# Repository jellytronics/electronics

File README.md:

electronics
===========

My electronics stuff

This project(s) will be suspended indefinitely from 11th March 2014.

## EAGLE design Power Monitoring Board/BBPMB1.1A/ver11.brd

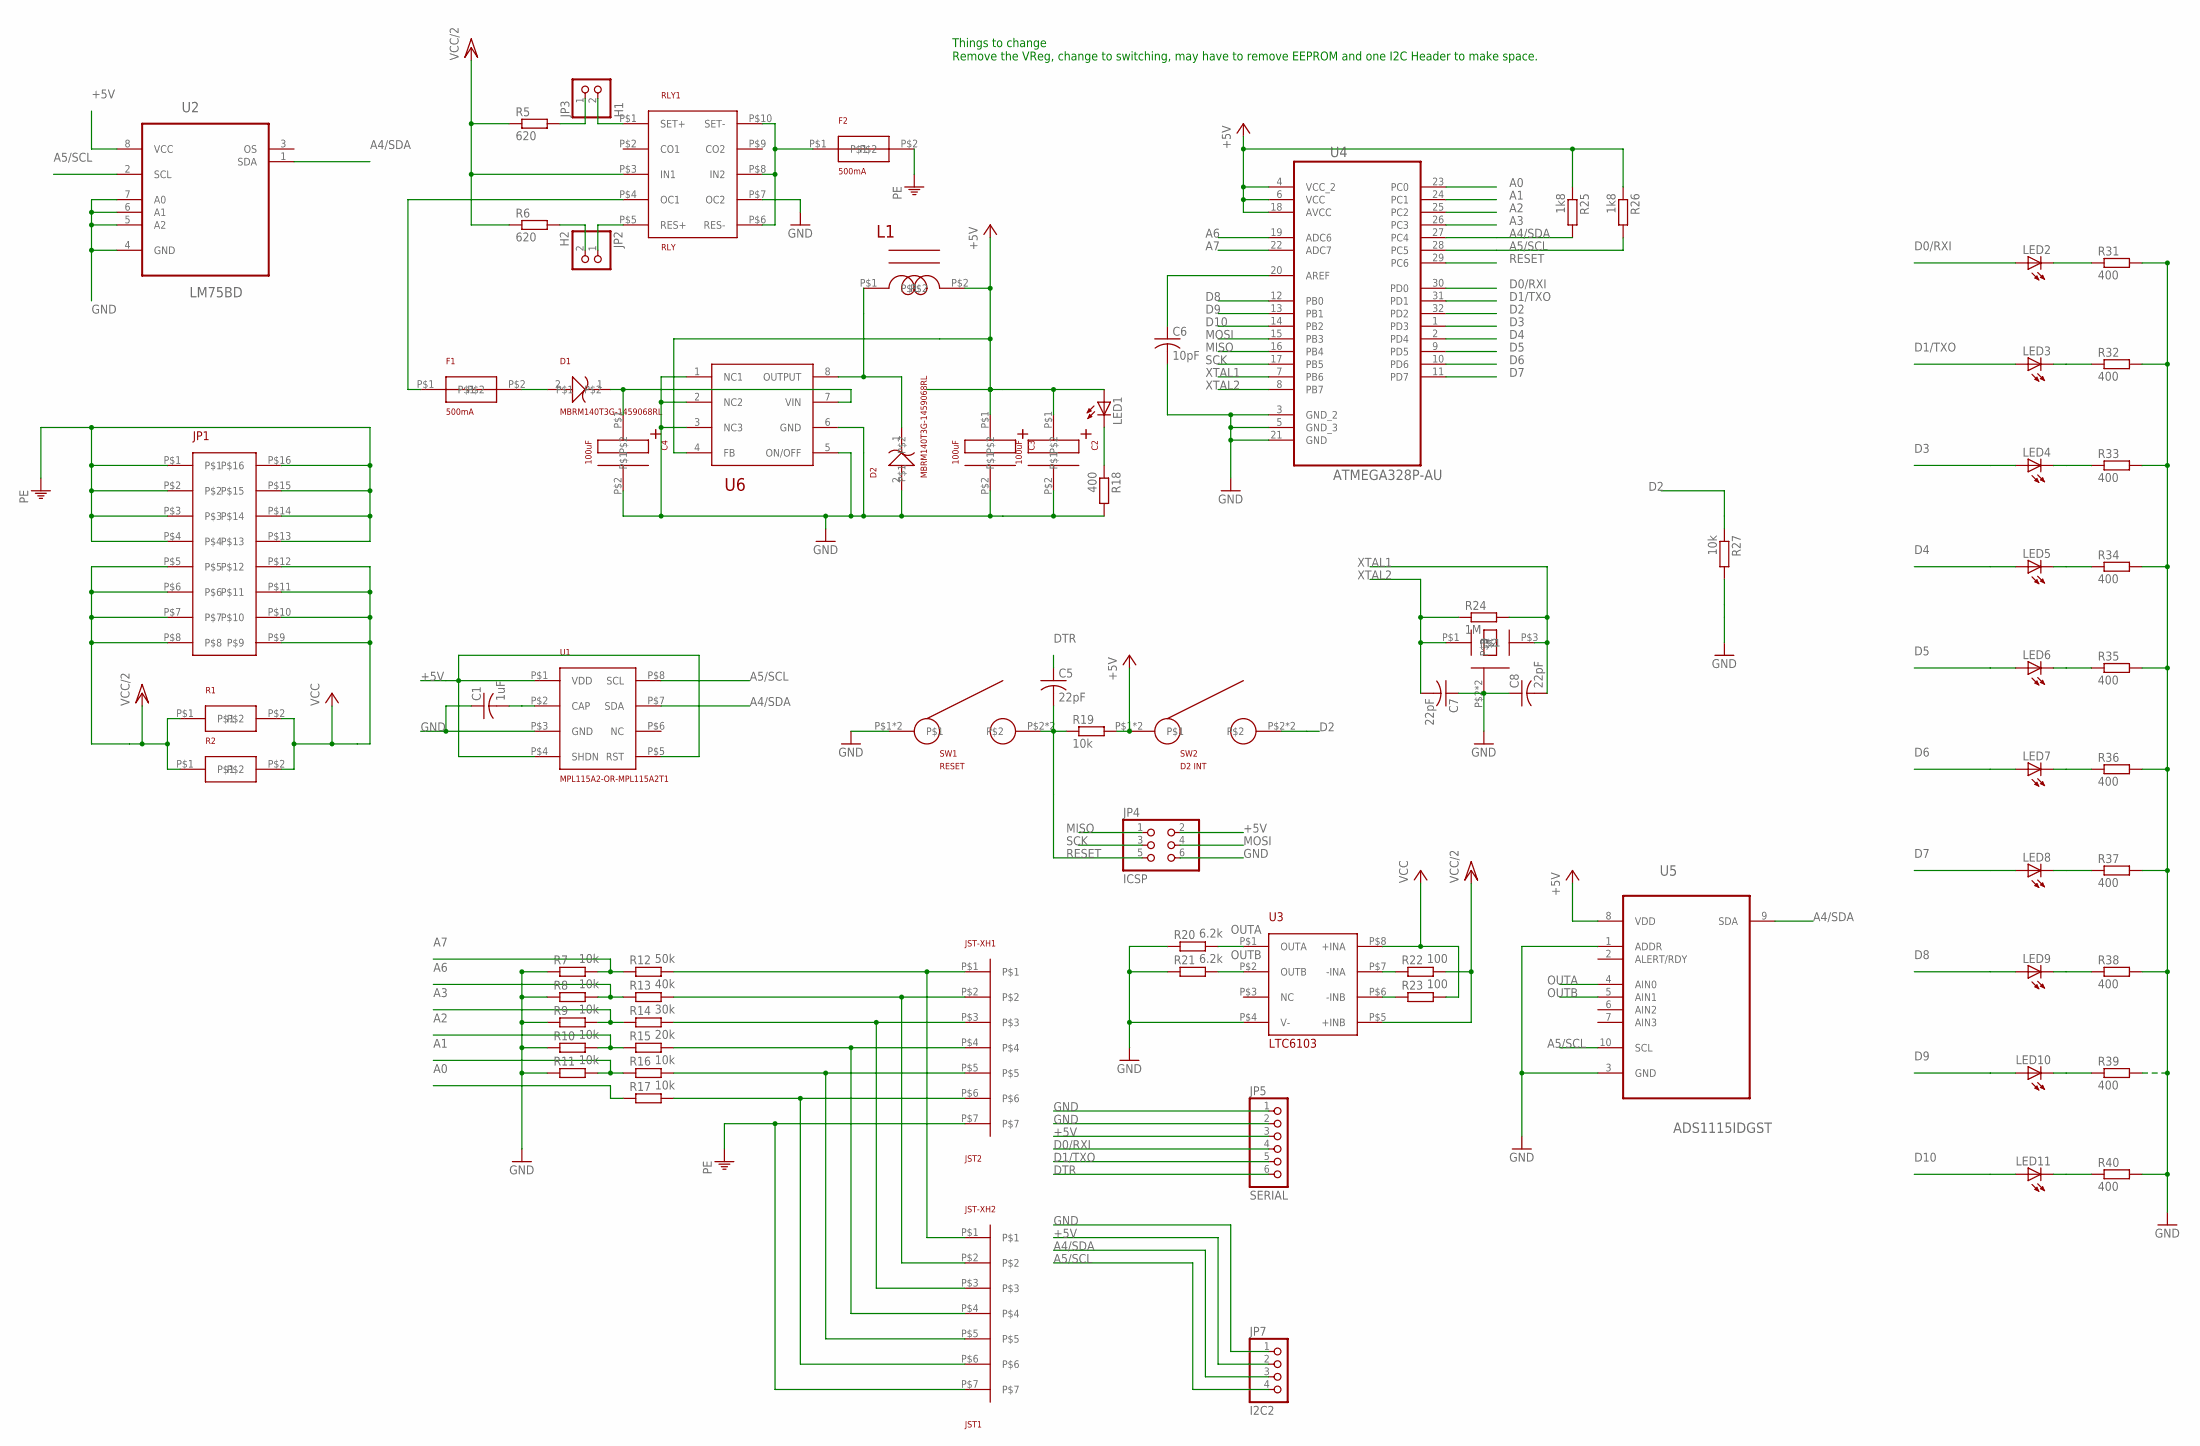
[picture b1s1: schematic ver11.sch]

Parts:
C1: 1uF; C1206
C2, C3, C4: 100uF; EEEFTH101XAP
C5, C7, C8: 22pF; C1206
C6: 10pF; C1206
D1, D2: MBRM140T3G-1459068RL
F1: 500mA; MF-MSMF050-2
F2: 500mA; 0154.500DR-FUSE-0453.500
JP1: 39-29-1167-MOLEX
JP2: H2; 1X02
JP3: H1; 1X02
JP4: ICSP; 2X03
JP5: SERIAL; 1X06
JP7: I2C2; 1X04
JST-XH1: JST2; JSTXH-7PIN
JST-XH2: JST1; JSTXH-7PIN
L1: MCSD75-121KU-120UF-INDUCTOR-660MA-1864147
LED1, LED2, LED3, LED4, LED5, LED6, LED7, LED8, LED9, LED10, LED11: LED1206; LED-1206
R1, R2: OARSXPR002FLF
R5, R6: 620; R1206
R7, R8, R9, R10, R11, R16, R17, R19, R27: 10k; R1206
R12: 50k; R1206
R13: 40k; R1206
R14: 30k; R1206
R15: 20k; R1206
R18, R31, R32, R33, R34, R35, R36, R37, R38, R39, R40: 400; R1206
R20, R21: 6.2k; R1206
R22, R23: 100; R1206
R24: 1M; R1206
R25, R26: 1k8; R1206
RLY1: RLY; 3-1393788-3
SW1: RESET; MC32829
SW2: D2 INT; MC32829
U1: MPL115A2-OR-MPL115A2T1
U2: LM75BD; SOIC127P600X175-8N
U3: LTC6103; LTC6103CMS8#PBF
U4: ATMEGA328P-AU; QFP80P900X900X120-32N
U5: ADS1115IDGST; SOP50P490X110-10N
U6: VOLTREG-LM2594MX-5.0/NOPB-1496090; SO08
XT1: ABMM2-16.000MHZ-E2-T

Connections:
+5V: C2.P$1, C3.P$1, JP4.2, JP5.3, JP7.2, L1.P$2, LED1.A, R19.2, R25.1, R26.1, SW2.P$1, SW2.P$4, U1.P$1 (VDD), U1.P$4 (SHDN), U1.P$5 (RST), U2.8 (VCC), U4.4 (VCC_2), U4.6 (VCC), U4.18 (AVCC), U5.8 (VDD), U6.4 (FB)
A0: R17.1, U4.23 (PC0)
A1: R11.2, R16.1, U4.24 (PC1)
A2: R10.2, R15.1, U4.25 (PC2)
A3: R9.2, R14.1, U4.26 (PC3)
A4/SDA: JP7.3, R25.2, U1.P$7 (SDA), U2.1 (SDA), U4.27 (PC4), U5.9 (SDA)
A5/SCL: JP7.4, R26.2, U1.P$8 (SCL), U2.2 (SCL), U4.28 (PC5), U5.10 (SCL)
A6: R8.2, R13.1, U4.19 (ADC6)
A7: R7.2, R12.1, U4.22 (ADC7)
D0/RXI: JP5.4, LED2.A, U4.30 (PD0)
D1/TXO: JP5.5, LED3.A, U4.31 (PD1)
D2: R27.1, SW2.P$2, SW2.P$3, U4.32 (PD2)
D3: LED4.A, U4.1 (PD3)
D4: LED5.A, U4.2 (PD4)
D5: LED6.A, U4.9 (PD5)
D6: LED7.A, U4.10 (PD6)
D7: LED8.A, U4.11 (PD7)
D8: LED9.A, U4.12 (PB0)
D9: LED10.A, U4.13 (PB1)
D10: LED11.A, U4.14 (PB2)
DTR: C5.1, JP5.6
GND: C1.1, C2.P$2, C3.P$2, C4.P$2, C6.2, C7.1, C8.1, D2.2, JP4.6, JP5.1, JP5.2, JP7.1, R7.1, R8.1, R9.1, R10.1, R11.1, R18.2, R20.1, R21.1, R27.2, R31.2, R32.2, R33.2, R34.2, R35.2, R36.2, R37.2, R38.2, R39.2, R40.2, RLY1.P$7 (OC2), SW1.P$1, SW1.P$4, U1.P$3 (GND), U2.4 (GND), U2.5 (A2), U2.6 (A1), U2.7 (A0), U3.P$4 (V-), U4.3 (GND_2), U4.5 (GND_3), U4.21 (GND), U5.1 (ADDR), U5.3 (GND), U6.1 (NC1), U6.2 (NC2), U6.3 (NC3), U6.5 (ON/OFF), U6.6 (GND), XT1.P$2, XT1.P$4
MISO: JP4.1, U4.16 (PB4)
MOSI: JP4.4, U4.15 (PB3)
unnamed: F1.P$1, RLY1.P$4 (OC1)
unnamed: C4.P$1, D1.1, U6.7 (VIN)
unnamed: D1.2, F1.P$2
unnamed: LED1.C, R18.1
unnamed: JP3.1, R5.2
unnamed: JP3.2, RLY1.P$1 (SET+)
unnamed: LED2.C, R31.1
unnamed: LED3.C, R32.1
unnamed: LED4.C, R33.1
unnamed: LED5.C, R34.1
unnamed: LED6.C, R35.1
unnamed: LED7.C, R36.1
unnamed: LED8.C, R37.1
unnamed: LED9.C, R38.1
unnamed: LED10.C, R39.1
unnamed: LED11.C, R40.1
unnamed: JST-XH1.P$1, JST-XH2.P$1, R12.2
unnamed: JST-XH1.P$2, JST-XH2.P$2, R13.2
unnamed: JST-XH1.P$3, JST-XH2.P$3, R14.2
unnamed: JST-XH1.P$4, JST-XH2.P$4, R15.2
unnamed: JST-XH1.P$5, JST-XH2.P$5, R16.2
unnamed: JST-XH1.P$6, JST-XH2.P$6, R17.2
unnamed: JP2.2, R6.2
unnamed: C6.1, U4.20 (AREF)
unnamed: F2.P$1, RLY1.P$6 (RES-), RLY1.P$8 (IN2), RLY1.P$10 (SET-)
unnamed: JP2.1, RLY1.P$5 (RES+)
unnamed: D2.1, L1.P$1, U6.8 (OUTPUT)
unnamed: R22.1, U3.P$7 (-INA)
unnamed: R23.1, U3.P$6 (-INB)
unnamed: C1.2, U1.P$2 (CAP)
OUTA: R20.2, U3.P$1 (OUTA), U5.4 (AIN0)
OUTB: R21.2, U3.P$2 (OUTB), U5.5 (AIN1)
PE: F2.P$2, JP1.P$1, JP1.P$2, JP1.P$3, JP1.P$4, JP1.P$13, JP1.P$14, JP1.P$15, JP1.P$16, JST-XH1.P$7, JST-XH2.P$7
RESET: C5.2, JP4.5, R19.1, SW1.P$2, SW1.P$3, U4.29 (PC6)
SCK: JP4.3, U4.17 (PB5)
VCC: JP1.P$9, JP1.P$10, JP1.P$11, JP1.P$12, R1.P$2, R2.P$2, R23.2, U3.P$8 (+INA)
VCC/2: JP1.P$5, JP1.P$6, JP1.P$7, JP1.P$8, R1.P$1, R2.P$1, R5.1, R6.1, R22.2, RLY1.P$3 (IN1), U3.P$5 (+INB)
XTAL1: C8.2, R24.2, U4.7 (PB6), XT1.P$3
XTAL2: C7.2, R24.1, U4.8 (PB7), XT1.P$1

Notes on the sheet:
Things to change Remove the VReg, change to switching, may have to remove EEPROM and one I2C Header to make space.

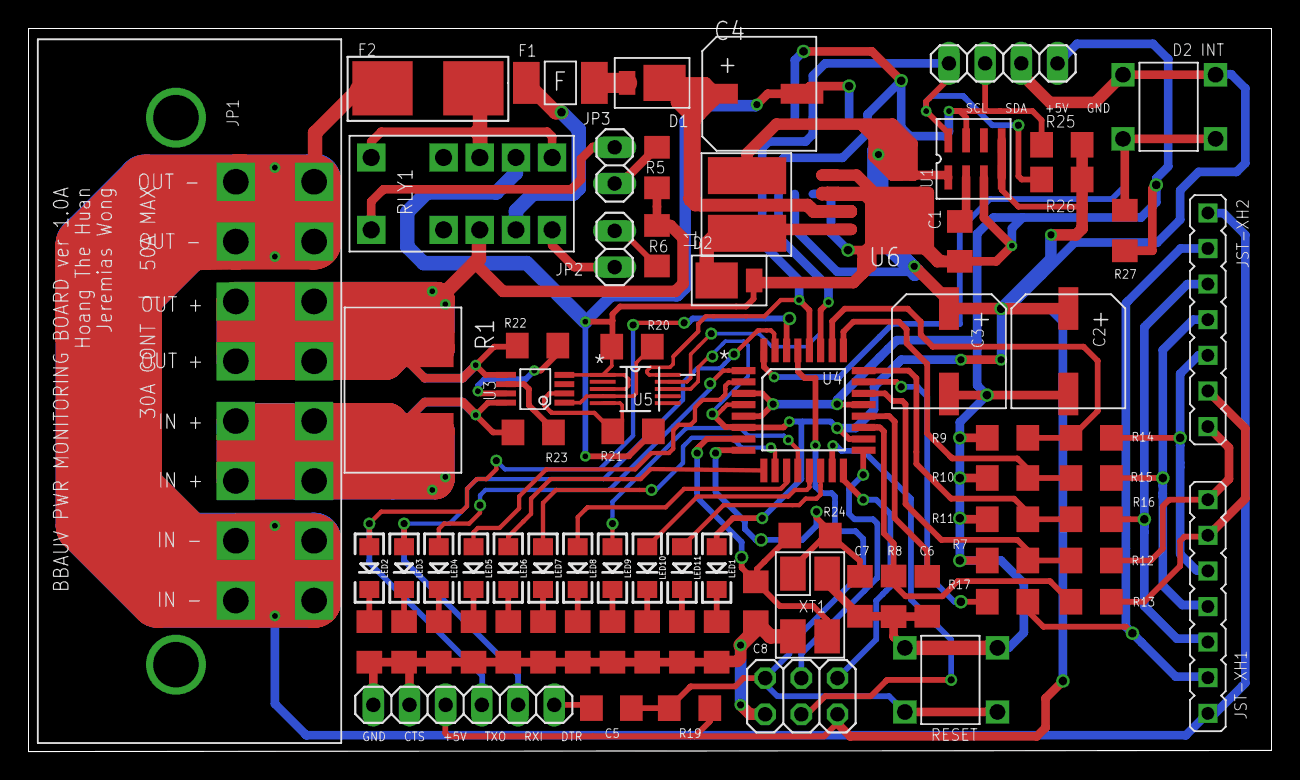
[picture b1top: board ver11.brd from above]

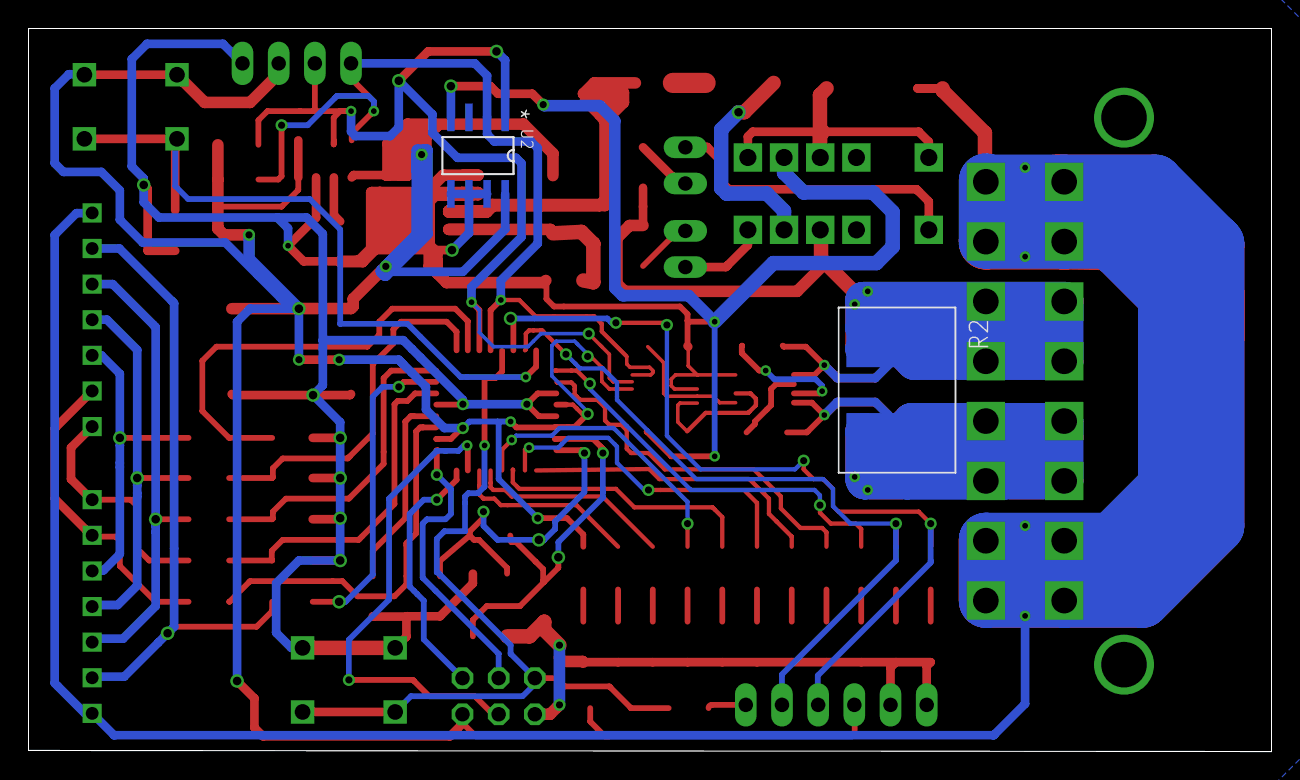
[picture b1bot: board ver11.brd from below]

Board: 2 copper layers, 87.3 x 50.8 mm, 77 parts (2 on the bottom side), 63 nets.

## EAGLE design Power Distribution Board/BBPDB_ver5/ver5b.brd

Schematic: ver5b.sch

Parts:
C1, C2, C3, C4, C18, C21, C22, C23, C24, C40: 0.5uF; C1206
C5, C6, C25, C26, C37, C38, C39: 22pF; C1206
C7, C8, C9, C10, C12, C30, C31, C34, C35: 10uF; C1206
C11, C20, C42, C44, C45, C49, C50, C51, C53, C54: EEEFTH101XAP
C13, C17: 1nF; C1206
C14: 2.2uF; C1206
C15, C16: 0.1uF; C1206
C19: 22uF; C1206
C27, C28, C32, C33: UVY2A221MHD1TO; E5-13
C29, C36, C41, C43, C46, C47, C48, C52: C-USC1206; C1206
C55: 10uF X7R; C1206
C56, C60: 1nF X7R; C1206
C57: 2.2uF X7R; C1206
C58, C59: 0.1uF X7R; C1206
C61: 22uF X7R; C1206
D1, D2, D3, D4, D5, D6, D7, D8, D9, D10: MBRM140T3G-1459068RL
F1, F3: 500mA; MF-MSMF050-2
F2, F4: 0154.500DR-FUSE-0453.500
IC1, IC2: FT4232HL; LQFP64
JP1: 39-29-1167-MOLEX
JP2: POWER IN; 39-29-1167-MOLEX
JP3, JP11: SERIAL_1; 1X03/90
JP4, JP12: SERIAL_2; 1X03/90
JP5, JP13: SERIAL_3; 1X03/90
JP6: HWSERIAL; 1X06
JP7: SBC_SW; 1X02
JP8: I2C; 1X04
JP9: PINHD-2X3; 2X03
JP10: ISCP; 2X03
JP14: SERIAL_4; 1X03/90
JP15, JP16: DC FAN 24V; 1X02
JP17: M4ATX | VBATT | 15A; 39-29-4049-MOLEX
JP18: POWER OUT :: M4 ATX | VIDEORAY | BTD150 | VVREG; 39-29-1167-MOLEX
JP19: 43045-2400
L1, L5: 6.8uH 2292530; LAIRD-TECH-INDUCTOR-TYS5040
L2, L6: 10uH 2292532; LAIRD-TECH-INDUCTOR-TYS5040
L3, L4: SER1360-802KLD-2288814RL-INDUCTOR
LED1, LED2, LED3, LED4, LED5, LED6, LED7, LED8, LED9, LED10, LED11, LED12, LED13, LED14, LED15: LEDCHIPLED_1206; CHIPLED_1206
R1, R24, R54, R55, R56, R57: 300; R1206
R2, R27, R39: 1M; R1206
R3, R4, R5, R6, R28, R29, R30, R31: 24; R1206
R7, R19, R20, R34: 1k; R1206
R8, R35: 12k; R1206
R9, R10, R36, R37: INDUCTOR-AISC-0603-R0082-J-T-1628488; R0603
R11, R21, R38, R50, R51: 100; R1206
R12, R15, R16, R17, R40, R41, R42, R43, R44, R45, R46, R47, R48, R49: 10k; R1206
R13, R66: 31.6k; R1206
R14, R23, R67, R70: 10.2k; R1206
R18, R68: 60.4k; R1206
R22, R69: 53.6k; R1206
R25, R26, R32, R33, R58, R59, R62, R63: 5000; R1206
R52, R53: 1k8; R1206
R60, R61, R64, R65: R-EU_R1206; R1206
SW1: RESET; MC32829
SW2: INT1; MC32829
SW3: INT2; MC32829
U1, U8: ADUM3160BRWZ; SOIC127P1032X265-16N
U2, U10: CAT93C46WI-GT3-1718152-EEPROM; SO08
U3, U18: LT3509EMSEPBF; SOP50P490X110-17N
U4, U5, U6, U12, U13, U14, U15: ISO7221ADR-1575146; SO08
U7: PS2701A-1-F3-A-1682859RL
U9: MPL115A2-OR-MPL115A2T1
U11: ATMEGA328P-AU; QFP80P900X900X120-32N
U16, U17: TPS5450DDARG4; SOIC127P600X170-9N
U$1, U$5: USB-MINIB-5PIN; USB-MINIB
U$2, U$6: ABMM2-12.000MHZ-E2-T; ABMM2-16.000MHZ-E2-T
U$7: ABMM2-16.000MHZ-E2-T
U$8, U$11, U$12, U$13: LTC4416
U$9, U$10, U$14, U$15, U$16, U$17, U$18, U$19, U$20, U$21, U$22, U$23, U$24, U$25, U$26, U$27: IRF9310PBF

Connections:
+1.8_A: C7.2, IC1.12 (VCORE), IC1.37 (VCORE), IC1.50 (VREGIN), IC1.64 (VCORE)
+1.8_B: C30.2, IC2.12 (VCORE), IC2.37 (VCORE), IC2.50 (VREGIN), IC2.64 (VCORE)
+3.3_A: C8.2, C11.P$1, C12.2, IC1.20 (VCCIO), IC1.31 (VCCIO), IC1.42 (VCCIO), IC1.49 (VREGOUT), IC1.56 (VCCIO), L1.1, LED2.A, R7.1, R9.1, R10.1, R12.1, R13.1, R16.1, R17.1, U2.2 (VCC), U2.8 (ORG)
+3.3_B: C31.2, C55.2, IC2.20 (VCCIO), IC2.31 (VCCIO), IC2.42 (VCCIO), IC2.49 (VREGOUT), IC2.56 (VCCIO), L5.1, R34.1, R36.1, R37.1, R46.1, R48.1, R49.1, R66.1, U10.2 (VCC), U10.8 (ORG)
+5V_A: C4.2, C18.2, C19.2, C20.P$1, C40.1, JP6.3, JP8.2, JP9.3, JP9.5, JP10.2, L2.2, LED3.A, R22.1, R38.2, R40.1, R42.1, R44.1, R52.2, R53.2, SW2.P$1, SW2.P$4, SW3.P$1, SW3.P$4, U1.16 (VBUS2), U3.13 (BD), U4.1 (VCC1), U4.8 (VCC2), U5.1 (VCC1), U5.8 (VCC2), U6.1 (VCC1), U6.8 (VCC2), U9.P$1 (VDD), U9.P$4 (SHDN), U9.P$5 (RST), U11.4 (VCC_2), U11.6 (VCC), U11.18 (AVCC)
+5V_B: C24.2, C61.2, L6.2, R69.1, U8.16 (VBUS2), U12.1 (VCC1), U12.8 (VCC2), U13.1 (VCC1), U13.8 (VCC2), U14.1 (VCC1), U14.8 (VCC2), U15.1 (VCC1), U15.8 (VCC2), U18.13 (BD), U$8.P$2 (E1)
A0: LED8.A, U11.23 (PC0)
A1: LED9.A, U11.24 (PC1)
A2: LED10.A, U11.25 (PC2)
A3: LED11.A, U11.26 (PC3)
A4/SDA: JP8.3, R52.1, U9.P$7 (SDA), U11.27 (PC4)
A5/SCL: JP8.4, R53.1, U9.P$8 (SCL), U11.28 (PC5)
A6: U11.19 (ADC6)
A7: U11.22 (ADC7)
D0/RXI: JP6.4, R19.1, U11.30 (PD0)
D1/TXO: JP6.5, R20.1, U11.31 (PD1)
D2: JP9.4, R50.1, SW2.P$2, SW2.P$3, U11.32 (PD2)
D3: JP9.6, R51.1, SW3.P$2, SW3.P$3, U11.1 (PD3)
D4: R41.2, U11.2 (PD4), U$11.P$4 (E2)
D5: R40.2, U11.9 (PD5), U$11.P$2 (E1)
D6: R45.2, U11.10 (PD6), U$13.P$4 (E2)
D7: R44.2, U11.11 (PD7), U$13.P$2 (E1)
D8: R43.2, U11.12 (PB0), U$12.P$4 (E2)
D9: R42.2, U11.13 (PB1), U$12.P$2 (E1)
D10: U7.P$1, U11.14 (PB2)
DTR: C36.1, IC1.55 (DB4/DTR), JP6.6
EECLK_A: IC1.62 (EECLK), R17.2, U2.4 (SK)
EECLK_B: IC2.62 (EECLK), R49.2, U10.4 (SK)
EECS_A: IC1.63 (EECS), R16.2, U2.3 (CS)
EECS_B: IC2.63 (EECS), R48.2, U10.3 (CS)
EEDATA_A: IC1.61 (EEDATA), R15.1, U2.6 (DO)
EEDATA_B: IC2.61 (EEDATA), R47.1, U10.6 (DO)
GND_A: C3.1, C4.1, C5.1, C6.1, C7.1, C8.1, C9.1, C10.1, C11.P$2, C12.1, C13.1, C14.1, C17.1, C18.1, C19.1, C20.P$2, C29.1, C37.1, C38.1, C39.2, C40.2, F2.P$2, IC1.1 (GND), IC1.5 (GND), IC1.10 (AGND), IC1.11 (GND), IC1.13 (TEST), IC1.15 (GND), IC1.25 (GND), IC1.35 (GND), IC1.47 (GND), IC1.51 (GND), JP6.1, JP6.2, JP8.1, JP9.1, JP10.6, R8.1, R11.1, R14.2, R18.2, R23.2, R24.1, R41.1, R43.1, R45.1, R50.2, R51.2, R54.1, R55.1, R56.1, R57.1, SW1.P$1, SW1.P$4, U1.9 (GND2_2), U1.15 (GND2), U2.7 (GND), U3.12 (SYNC), U3.14 (AGND), U3.17 (EP), U4.4 (GND1), U5.4 (GND1), U6.4 (GND1), U7.P$2, U9.P$3 (GND), U11.3 (GND_2), U11.5 (GND_3), U11.21 (GND), U$2.P$2, U$2.P$4, U$7.P$2, U$7.P$4
GND_B: C23.1, C24.1, C25.1, C26.1, C30.1, C31.1, C34.1, C35.1, C55.1, C56.1, C57.1, C60.1, C61.1, F4.P$2, IC2.1 (GND), IC2.5 (GND), IC2.10 (AGND), IC2.11 (GND), IC2.13 (TEST), IC2.15 (GND), IC2.25 (GND), IC2.35 (GND), IC2.47 (GND), IC2.51 (GND), R35.1, R67.2, R68.2, R70.2, U8.9 (GND2_2), U8.15 (GND2), U10.7 (GND), U12.4 (GND1), U13.4 (GND1), U14.4 (GND1), U15.4 (GND1), U18.12 (SYNC), U18.14 (AGND), U18.17 (EP), U$6.P$2, U$6.P$4
IND+: R6.2, U$1.D+
IND+_B: R31.2, U$5.D+
IND-: R5.2, U$1.D-
IND-_B: R30.2, U$5.D-
MISO: JP10.1, U11.16 (PB4)
MOSI: JP10.4, U11.15 (PB3)
unnamed: U$20.P$1 (S), U$20.P$2 (S), U$20.P$3 (S), U$26.P$1 (S), U$26.P$2 (S), U$26.P$3 (S)
unnamed: U$21.P$1 (S), U$21.P$2 (S), U$21.P$3 (S), U$27.P$1 (S), U$27.P$2 (S), U$27.P$3 (S)
unnamed: U$13.P$10 (G1), U$20.P$4 (G), U$26.P$4 (G)
unnamed: U$13.P$6 (G2), U$21.P$4 (G), U$27.P$4 (G)
unnamed: C57.2, F3.P$2, U18.4 (VIN_2), U18.5 (VIN)
unnamed: C58.1, D5.2, L5.2, U18.3 (SW1)
unnamed: D9.2, D10.2, F3.P$1
unnamed: LED6.C, R32.2
unnamed: LED8.C, R54.2
unnamed: LED14.C, R62.1
unnamed: LED7.C, R33.2
unnamed: U$18.P$1 (S), U$18.P$2 (S), U$18.P$3 (S), U$24.P$1 (S), U$24.P$2 (S), U$24.P$3 (S)
unnamed: U$19.P$1 (S), U$19.P$2 (S), U$19.P$3 (S), U$25.P$1 (S), U$25.P$2 (S), U$25.P$3 (S)
unnamed: U$12.P$10 (G1), U$18.P$4 (G), U$24.P$4 (G)
unnamed: U$12.P$6 (G2), U$19.P$4 (G), U$25.P$4 (G)
unnamed: C59.1, D6.2, L6.1, U18.6 (SW2)
unnamed: U$9.P$1 (S), U$9.P$2 (S), U$9.P$3 (S), U$14.P$1 (S), U$14.P$2 (S), U$14.P$3 (S)
unnamed: R68.1, U18.11 (RT)
unnamed: U$16.P$1 (S), U$16.P$2 (S), U$16.P$3 (S), U$22.P$1 (S), U$22.P$2 (S), U$22.P$3 (S)
unnamed: U$17.P$1 (S), U$17.P$2 (S), U$17.P$3 (S), U$23.P$1 (S), U$23.P$2 (S), U$23.P$3 (S)
unnamed: U$11.P$10 (G1), U$16.P$4 (G), U$22.P$4 (G)
unnamed: U$11.P$6 (G2), U$17.P$4 (G), U$23.P$4 (G)
unnamed: LED9.C, R55.2
unnamed: LED10.C, R56.2
unnamed: LED11.C, R57.2
unnamed: C56.2, U18.15 (RUN/SS1)
unnamed: C60.2, U18.10 (RUN/SS2)
unnamed: C29.2, U9.P$2 (CAP)
unnamed: C14.2, F1.P$2, U3.4 (VIN_2), U3.5 (VIN)
unnamed: R69.2, R70.1, U18.9 (FB2)
unnamed: R66.2, R67.1, U18.16 (FB1)
unnamed: C15.1, D1.2, L1.2, U3.3 (SW1)
unnamed: D5.1, U18.1 (DA1)
unnamed: C58.2, U18.2 (BOOST1)
unnamed: C59.2, U18.7 (BOOST2)
unnamed: IC1.53 (DB2/RTS), R21.2
unnamed: D6.1, U18.8 (DA2)
unnamed: C16.1, D2.2, L2.1, U3.6 (SW2)
unnamed: U$10.P$1 (S), U$10.P$2 (S), U$10.P$3 (S), U$15.P$1 (S), U$15.P$2 (S), U$15.P$3 (S)
unnamed: U$8.P$10 (G1), U$9.P$4 (G), U$14.P$4 (G)
unnamed: U$8.P$6 (G2), U$10.P$4 (G), U$15.P$4 (G)
unnamed: LED4.C, R25.2
unnamed: LED5.C, R26.2
unnamed: IC1.52 (DB1/RXD), R20.2
unnamed: IC1.48 (DB0/TXD), R19.2
unnamed: C21.2, U8.3 (VDD1), U8.4 (PDEN), U8.5 (SPU)
unnamed: LED13.C, R59.2
unnamed: LED12.C, R58.2
unnamed: C13.2, U3.15 (RUN/SS1)
unnamed: D7.2, D8.2, F1.P$1
unnamed: JP7.2, U7.P$3
unnamed: C17.2, U3.10 (RUN/SS2)
unnamed: R22.2, R23.1, U3.9 (FB2)
unnamed: R13.2, R14.1, U3.16 (FB1)
unnamed: D1.1, U3.1 (DA1)
unnamed: C15.2, U3.2 (BOOST1)
unnamed: C16.2, U3.7 (BOOST2)
unnamed: D2.1, U3.8 (DA2)
unnamed: R18.1, U3.11 (RT)
unnamed: C1.1, C2.1, R1.1, U1.2 (GND1_2), U1.8 (GND1), U$1.GND
unnamed: C3.2, U1.12 (PIN), U1.13 (SPD), U1.14 (VDD2)
unnamed: R3.1, U1.11 (DD-)
unnamed: C1.2, U1.3 (VDD1), U1.4 (PDEN), U1.5 (SPU)
unnamed: C2.2, LED1.A, U1.1 (VBUS1), U$1.VBUS
unnamed: R4.1, U1.10 (DD+)
unnamed: IC1.8 (USBDP), R4.2
unnamed: IC1.7 (USBDM), R3.2
unnamed: R5.1, U1.6 (UD-)
unnamed: R6.1, U1.7 (UD+)
unnamed: IC1.6 (REF), R8.2
unnamed: C10.2, IC1.4 (VPHY), R9.2
unnamed: C9.2, IC1.9 (VPLL), R10.2
unnamed: IC1.14 (RESET#), R7.2
unnamed: C22.2, U8.1 (VBUS1), U$5.VBUS
unnamed: C21.1, C22.1, U8.2 (GND1_2), U8.8 (GND1), U$5.GND
unnamed: R12.2, R15.2, U2.5 (DI)
unnamed: C39.1, U11.20 (AREF)
unnamed: C23.2, U8.12 (PIN), U8.13 (SPD), U8.14 (VDD2)
unnamed: IC2.8 (USBDP), R29.2
unnamed: IC2.7 (USBDM), R28.2
unnamed: R28.1, U8.11 (DD-)
unnamed: R29.1, U8.10 (DD+)
unnamed: R30.1, U8.6 (UD-)
unnamed: R31.1, U8.7 (UD+)
unnamed: IC2.16 (DB0/TXD), U12.3 (INB)
unnamed: IC2.17 (DB1/RXD), U12.2 (OUTA)
unnamed: JP11.1, U12.7 (INA)
unnamed: IC2.26 (DB0/TXD), U13.3 (INB)
unnamed: JP11.2, U12.6 (OUTB)
unnamed: IC1.16 (DB0/TXD), U4.3 (INB)
unnamed: IC2.27 (DB1/RXD), U13.2 (OUTA)
unnamed: IC2.38 (DB0/TXD), U14.3 (INB)
unnamed: IC2.39 (DB1/RXD), U14.2 (OUTA)
unnamed: IC2.48 (DB0/TXD), U15.3 (INB)
unnamed: JP11.3, U12.5 (GND2)
unnamed: JP12.1, U13.7 (INA)
unnamed: JP12.2, U13.6 (OUTB)
unnamed: R46.2, R47.2, U10.5 (DI)
unnamed: C35.2, IC2.4 (VPHY), R36.2
unnamed: C34.2, IC2.9 (VPLL), R37.2
unnamed: IC2.6 (REF), R35.2
unnamed: IC2.14 (RESET#), R34.2
unnamed: JP12.3, U13.5 (GND2)
unnamed: JP13.1, U14.7 (INA)
unnamed: JP13.2, U14.6 (OUTB)
unnamed: JP13.3, U14.5 (GND2)
unnamed: JP14.1, U15.7 (INA)
unnamed: JP14.2, U15.6 (OUTB)
unnamed: JP14.3, U15.5 (GND2)
unnamed: IC2.52 (DB1/RXD), U15.2 (OUTA)
unnamed: IC1.17 (DB1/RXD), U4.2 (OUTA)
unnamed: IC1.26 (DB0/TXD), U5.3 (INB)
unnamed: IC1.27 (DB1/RXD), U5.2 (OUTA)
unnamed: IC1.38 (DB0/TXD), U6.3 (INB)
unnamed: IC1.39 (DB1/RXD), U6.2 (OUTA)
unnamed: C52.2, C54.P$1, JP18.P$15, L4.2, LED14.A, R64.2
unnamed: LED15.C, R63.1
unnamed: JP7.1, U7.P$4
unnamed: C46.2, U17.1 (BOOT)
unnamed: C46.1, D4.2, L4.1, U17.8 (PH)
unnamed: C41.2, U16.1 (BOOT)
unnamed: C41.1, D3.2, L3.1, U16.8 (PH)
unnamed: C48.2, C49.P$1, JP19.2, L3.2, R60.2
unnamed: R60.1, R61.2, U16.4 (VSENSE)
unnamed: LED3.C, R24.2
unnamed: R64.1, R65.2, U17.4 (VSENSE)
unnamed: LED1.C, R1.2
unnamed: LED2.C, R11.2
unnamed: C42.P$1, C43.2, JP15.1, JP17.P$1, JP17.P$2, U16.7 (VIN), U$8.P$8 (VS), U$14.P$5 (D), U$14.P$6 (D), U$14.P$7 (D), U$14.P$8 (D), U$15.P$5 (D), U$15.P$6 (D), U$15.P$7 (D), U$15.P$8 (D)
PE: C32.-, C33.-, C44.P$2, C45.P$2, C47.1, C50.P$2, C52.1, C54.P$2, D4.1, F2.P$1, JP2.P$1, JP2.P$2, JP2.P$3, JP2.P$4, JP2.P$13, JP2.P$14, JP2.P$15, JP2.P$16, JP16.1, JP18.P$2, JP18.P$4, JP18.P$6, JP18.P$8, JP18.P$10, JP18.P$12, JP18.P$14, JP18.P$16, R32.1, R33.1, R58.1, R59.1, R62.2, R63.2, R65.1, U17.6 (GND), U17.9 (EP), U$11.P$3 (GND), U$12.P$3 (GND), U$13.P$3 (GND)
PE_B: C27.-, C28.-, C42.P$2, C43.1, C48.1, C49.P$2, C51.P$2, C53.P$2, D3.1, F4.P$1, JP1.P$1, JP1.P$2, JP1.P$3, JP1.P$4, JP1.P$13, JP1.P$14, JP1.P$15, JP1.P$16, JP15.2, JP17.P$3, JP17.P$4, JP19.1, JP19.3, JP19.5, JP19.7, JP19.9, JP19.11, JP19.13, JP19.15, JP19.17, JP19.19, JP19.21, JP19.23, R25.1, R26.1, R61.1, U16.6 (GND), U16.9 (EP), U$8.P$3 (GND), U$8.P$4 (E2)
RESET: C36.2, JP9.2, JP10.5, R21.1, R38.1, SW1.P$2, SW1.P$3, U11.29 (PC6)
RX_1: JP3.2, U4.6 (OUTB)
RX_2: JP4.2, U5.6 (OUTB)
RX_3: JP5.2, U6.6 (OUTB)
SCK: JP10.3, U11.17 (PB5)
SGND_1: JP3.3, U4.5 (GND2)
SGND_2: JP4.3, U5.5 (GND2)
SGND_3: JP5.3, U6.5 (GND2)
TX_1: JP3.1, U4.7 (INA)
TX_2: JP4.1, U5.7 (INA)
TX_3: JP5.1, U6.7 (INA)
VBATT_1A: C33.+, D8.1, JP2.P$5, JP2.P$6, JP2.P$7, JP2.P$8, LED7.A, U$11.P$7 (V2), U$12.P$7 (V2), U$13.P$7 (V2), U$17.P$5 (D), U$17.P$6 (D), U$17.P$7 (D), U$17.P$8 (D), U$19.P$5 (D), U$19.P$6 (D), U$19.P$7 (D), U$19.P$8 (D), U$21.P$5 (D), U$21.P$6 (D), U$21.P$7 (D), U$21.P$8 (D)
VBATT_1B: C28.+, C51.P$1, D9.1, JP1.P$5, JP1.P$6, JP1.P$7, JP1.P$8, JP19.4, JP19.6, JP19.8, JP19.10, JP19.12, LED5.A, U$8.P$7 (V2), U$10.P$5 (D), U$10.P$6 (D), U$10.P$7 (D), U$10.P$8 (D)
VBATT_2A: C32.+, D7.1, JP2.P$9, JP2.P$10, JP2.P$11, JP2.P$12, LED6.A, U$11.P$9 (V1), U$12.P$9 (V1), U$13.P$9 (V1), U$16.P$5 (D), U$16.P$6 (D), U$16.P$7 (D), U$16.P$8 (D), U$18.P$5 (D), U$18.P$6 (D), U$18.P$7 (D), U$18.P$8 (D), U$20.P$5 (D), U$20.P$6 (D), U$20.P$7 (D), U$20.P$8 (D)
VBATT_2B: C27.+, C53.P$1, D10.1, JP1.P$9, JP1.P$10, JP1.P$11, JP1.P$12, JP19.14, JP19.16, JP19.18, JP19.20, JP19.22, JP19.24, LED4.A, U$8.P$9 (V1), U$9.P$5 (D), U$9.P$6 (D), U$9.P$7 (D), U$9.P$8 (D)
V_1A: C45.P$1, JP18.P$7, JP18.P$9, LED13.A, U$13.P$8 (VS), U$26.P$5 (D), U$26.P$6 (D), U$26.P$7 (D), U$26.P$8 (D), U$27.P$5 (D), U$27.P$6 (D), U$27.P$7 (D), U$27.P$8 (D)
V_2A: C44.P$1, JP16.2, JP18.P$1, JP18.P$3, JP18.P$5, LED12.A, U$12.P$8 (VS), U$24.P$5 (D), U$24.P$6 (D), U$24.P$7 (D), U$24.P$8 (D), U$25.P$5 (D), U$25.P$6 (D), U$25.P$7 (D), U$25.P$8 (D)
V_3A: C47.2, C50.P$1, JP18.P$11, JP18.P$13, LED15.A, U17.7 (VIN), U$11.P$8 (VS), U$22.P$5 (D), U$22.P$6 (D), U$22.P$7 (D), U$22.P$8 (D), U$23.P$5 (D), U$23.P$6 (D), U$23.P$7 (D), U$23.P$8 (D)
XTAL1: C37.2, R39.1, U11.7 (PB6), U$7.P$1
XTAL2: C38.2, R39.2, U11.8 (PB7), U$7.P$3
XTAL3: C5.2, IC1.3 (XTOUT), R2.1, U$2.P$1
XTAL4: C6.2, IC1.2 (XTIN), R2.2, U$2.P$3
XTAL5: C25.2, IC2.3 (XTOUT), R27.1, U$6.P$1
XTAL6: C26.2, IC2.2 (XTIN), R27.2, U$6.P$3

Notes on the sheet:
Things to include Adjustable Voltage Regulator 2102646 Better MOSFETS reed switch stuff. breakaway Interface Isolation btw PMB, PDB and EC Caps and Inductors Fuse FAN - SP402024M-W Link all thrusters to same batt?

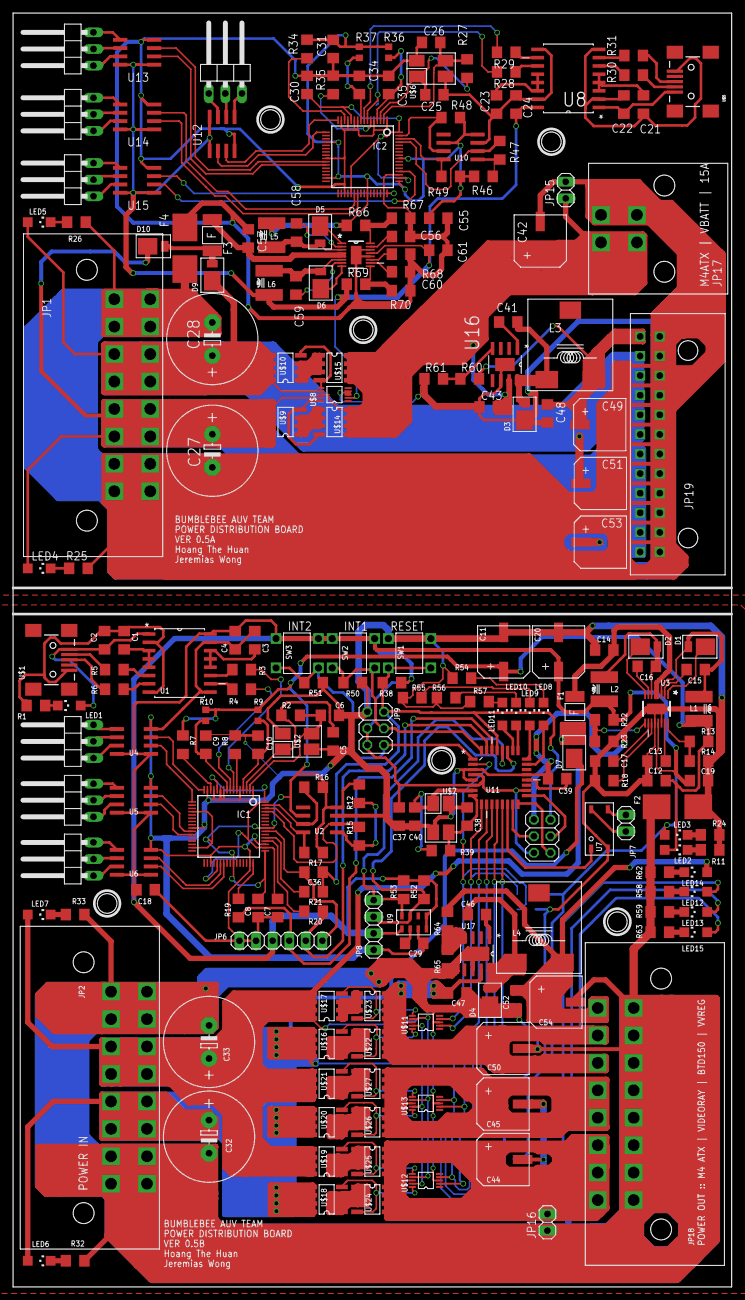
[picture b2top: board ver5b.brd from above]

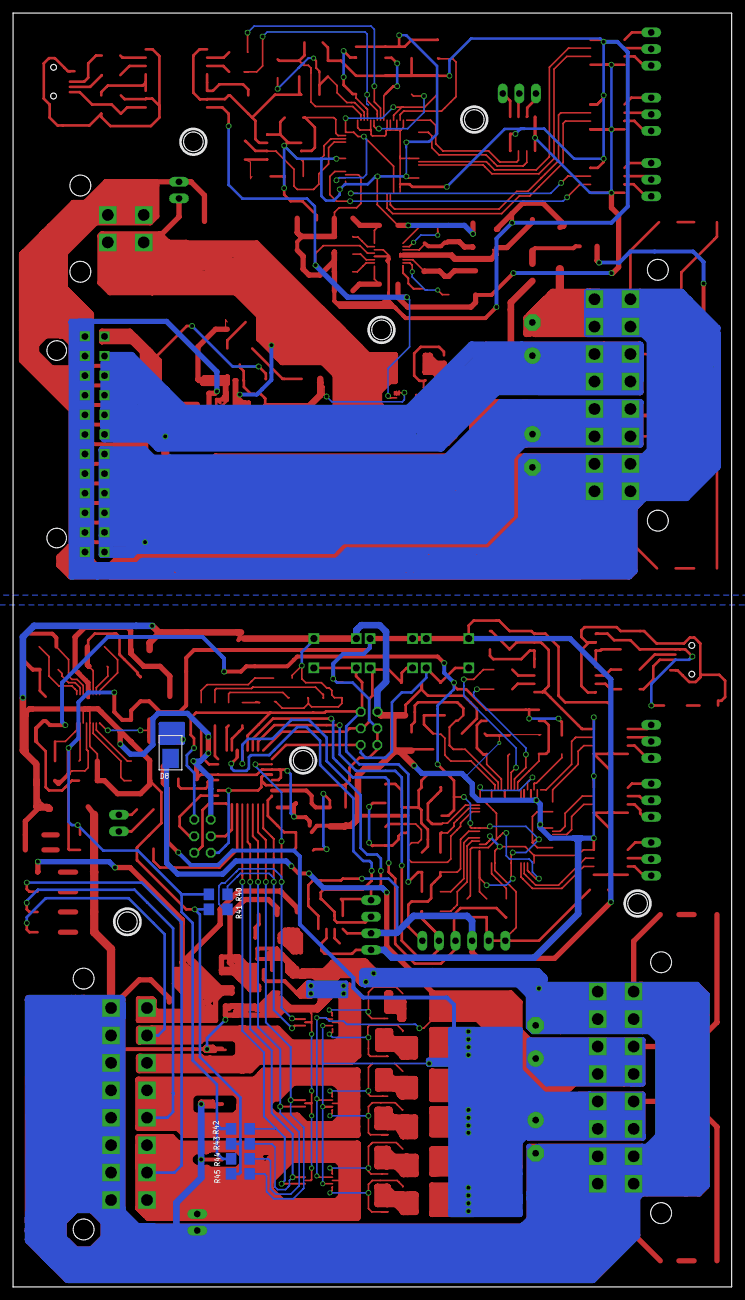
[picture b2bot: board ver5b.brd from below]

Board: 4 copper layers, 110.0 x 195.0 mm, 233 parts (7 on the bottom side), 193 nets.

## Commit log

2014-01-23 inital commit of PCB boards

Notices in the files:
parts and their libraries:
SparkFun-Connectors: Licensing: CC v3.0 Share-Alike You are welcome to use this library for commercial purposes.
